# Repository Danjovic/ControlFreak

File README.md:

# ControlFreak
Collection of firmware and schematics for connecting retro Joysticks and Gamepads to USB port.

The base circuit uses a cheap Arduino Pro Micro that come up with an ATMega32U4 chip that yields native USB connectivity.

||
|:--:|
| *Arduino Pro Micro* |

Such board combined with [HID-Project](https://github.com/NicoHood/HID) provides classes for several HID devices including a resourceful game controller with 6 analog axes, 32 buttons and a 2 Dpads.

|
|:--:|
| *Buttons and Axes on Windows* |

|
|:--:|
| *Buttons and Axes on Linux* |

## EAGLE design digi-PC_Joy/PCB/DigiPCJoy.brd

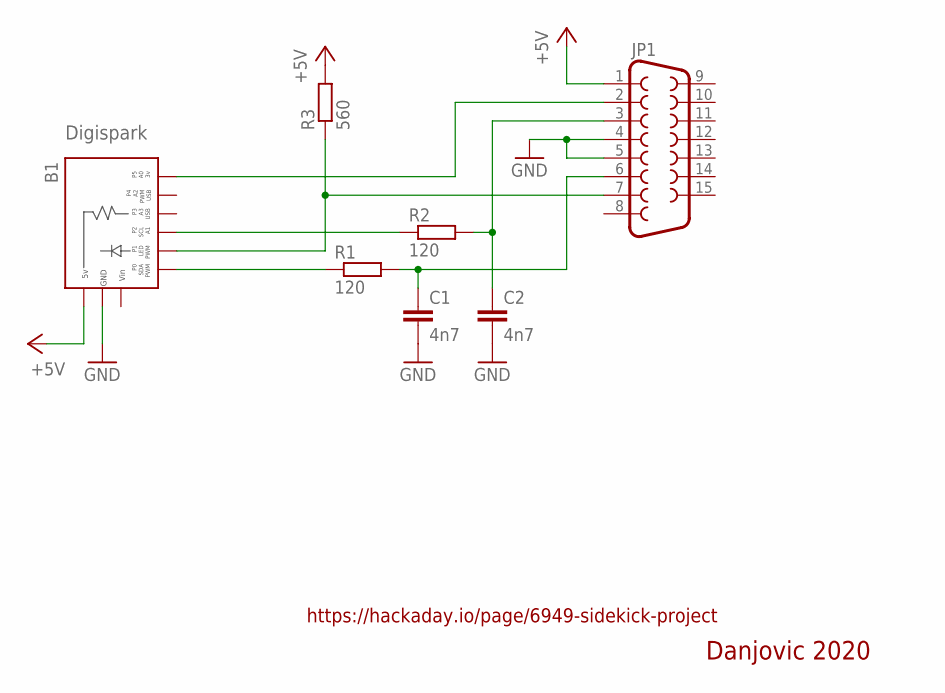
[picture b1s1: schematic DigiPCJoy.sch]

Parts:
B1: Digispark; DIGISPARK_SOCKET
C1, C2: 4n7; C050-024X044
JP1: F15H
R1, R2: 120; 0204/7
R3: 560; 0204/7

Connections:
+5V: B1.5V, JP1.1, R3.2
GND: B1.GND, C1.2, C2.2, JP1.4, JP1.5
unnamed: B1.P5, JP1.2
unnamed: C1.1, JP1.6, R1.2
unnamed: C2.1, JP1.3, R2.2
P0: B1.P0, R1.1
P1: B1.P1, JP1.7, R3.1
P2: B1.P2, R2.1
VIN: B1.VIN

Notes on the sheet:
Danjovic 2020
https://hackaday.io/page/6949-sidekick-project
Digispark

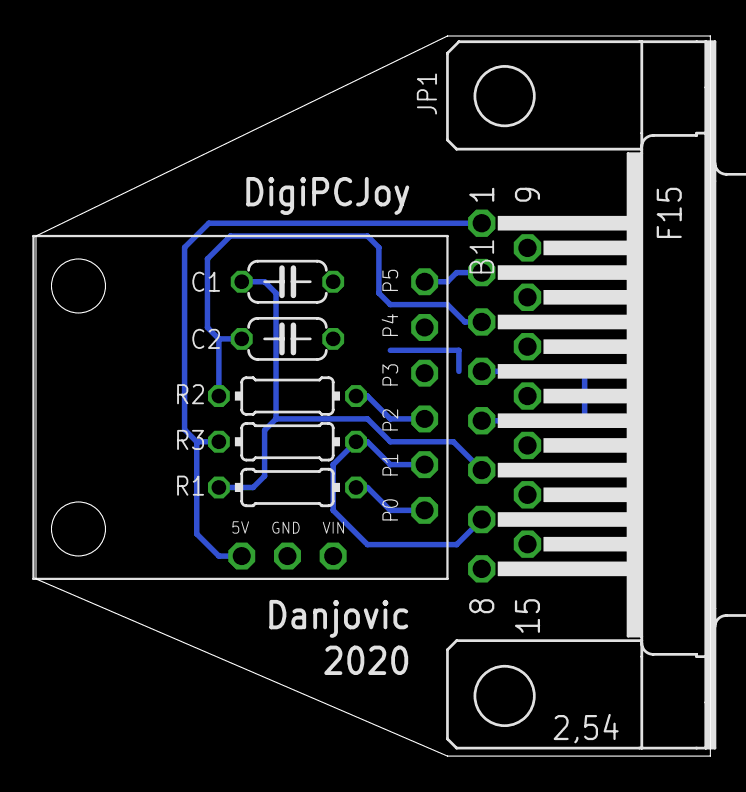
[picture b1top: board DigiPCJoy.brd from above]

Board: 2 copper layers, 37.5 x 40.0 mm, 7 parts (0 on the bottom side), 8 nets.

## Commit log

2020-04-12 upload files, wip
2020-04-12 Working version
2020-04-12 Picture update
2020-04-13 Added safe guard for connecting the controller without the axis connected.
2020-04-15 Sidekick PC joystick with digispark
2020-04-16 Move schematic to project directory
2020-04-16 Added schematic
2020-04-16 Added Sega controller firmware and schematic
2020-04-16 bug correction
2020-04-18 Added NES/SNES controller adapter
2020-04-19 Added PCB boards for sidekick project with digispark
2020-04-19 Updadet footprint of digispark board with USB connector
2020-04-19 updated digispark footprint
2020-05-03 Added Atari 2600 controllers support
